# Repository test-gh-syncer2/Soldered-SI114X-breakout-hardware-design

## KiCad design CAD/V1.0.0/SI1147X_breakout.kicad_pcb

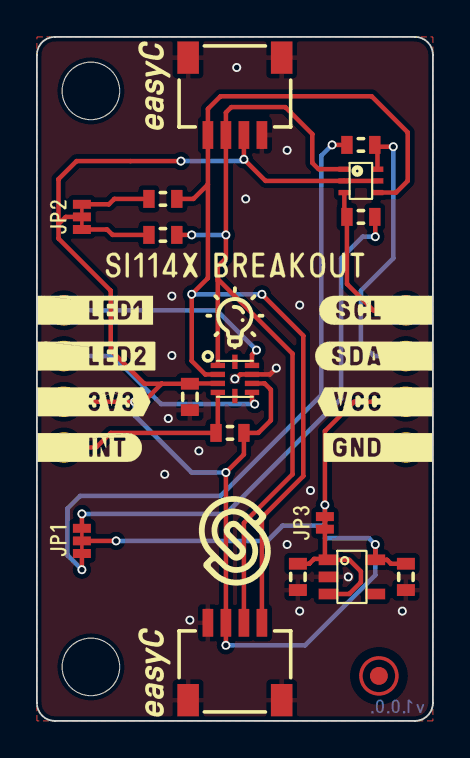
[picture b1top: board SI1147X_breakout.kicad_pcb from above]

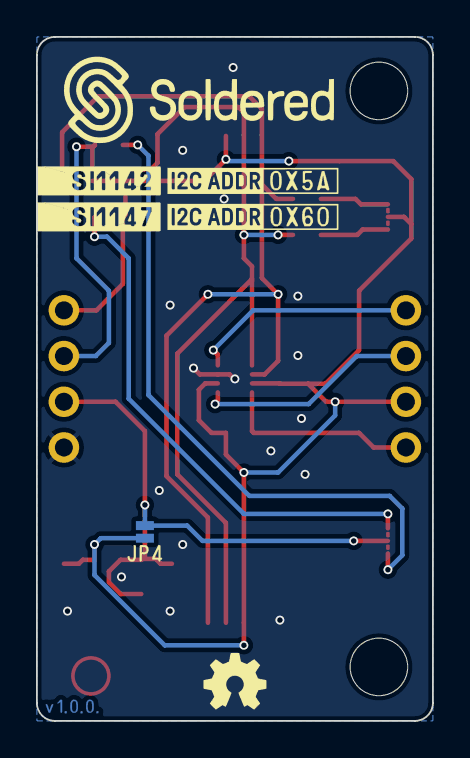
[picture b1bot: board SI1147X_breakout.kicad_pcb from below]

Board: 2 copper layers, 22.0 x 38.0 mm, 23 parts (2 on the bottom side), 15 nets.

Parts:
C1: 0.1uF; 0603C
C2, C3: 2.2uF; 0603C
FD1: FIDUCIAL; FIDUCIAL_23
H1, H2: HOLE_3.2mm
JP1, JP2: SMD_JUMPER_3_PAD_TRACE
JP3: SMD-JUMPER-CONNECTED_TRACE_SLODERMASK
JP4: SMD_JUMPER
K1, K3: HEADER_MALE_4X1
K2, K4: easyC-SMD; easyC-connector
R1, R2, R3, R4, R5: 10k; 0603R
Ref**: Val**; Version1.0.0.
U1: SI1142-A11-GM
U2: NMOS-DUAL; SOT-363
U3: SE5218; SOT-23-5

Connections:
3V3: C1.2, C3.2, JP2.2, JP4.2, K1.2, K2.3 (3V3), K4.3 (3V3), R1.1, U1.3 (VDD), U1.7 (LED3), U2.2 (G2), U2.5 (G1), U3.5 (VOUT)
5V: JP1.2, JP3.2, JP4.1, K3.2
GND: C1.1, C2.1, C3.1, K2.4 (GND), K2.5 (SHIELD), K3.1, K4.4 (GND), K4.5 (SHIELD), U1.8 (GND), U3.2 (GND)
INT: K1.1, R1.2, U1.4 (INT)
LED1: K1.4, U1.9 (LED1)
LED2: K1.3, U1.6 (LED2)
unnamed: C2.2, JP3.1, U3.1 (VIN), U3.3 (EN)
SCL3,3: K2.1 (SCL), K4.1 (SCL), R5.1, U1.2 (SCL), U2.4 (S1)
SCL5: K3.4, R3.2, U2.3 (D1)
SCL_PULL3,3: JP2.1, R5.2
SCL_PULL5: JP1.1, R3.1
SDA3,3: K2.2 (SDA), K4.2 (SDA), R2.2, U1.1 (SDA), U2.1 (S2)
SDA5: K3.3, R4.1, U2.6 (D2)
SDA_PULL3,3: JP2.3, R2.1
SDA_PULL5: JP1.3, R4.2

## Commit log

2021-09-23 Syncing to git
2021-09-23 Updating open source files.
